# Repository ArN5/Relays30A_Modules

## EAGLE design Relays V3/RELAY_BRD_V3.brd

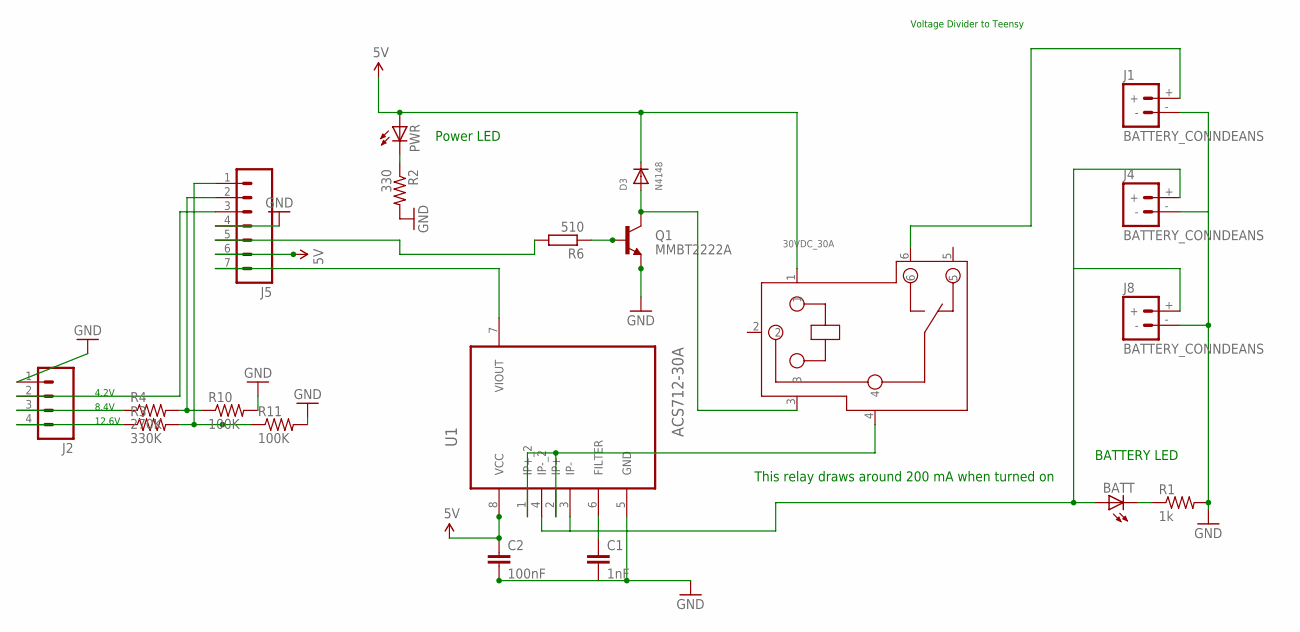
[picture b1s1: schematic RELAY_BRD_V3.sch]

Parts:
30VDC_30A: RELAY-SLA-05VDC-SL-C; 6P-19.8H
BATT: LED_E; LED_1206
C1: 1nF; 1206
C2: 100nF; 1206
D3: N4148; DO-1N4148
J1, J4, J8: BATTERY_CONNDEANS; DEANS
J2: M04POLAR; MOLEX-1X4
J5: M07LOCK_LONGPADS; 1X07_LOCK_LONGPADS
PWR: LED_E; LED_1206
Q1: MMBT2222A; SOT23-3
R1: 1k; 1206
R2: 330; 1206
R3: 330K; 1206
R4: 270K; 1206
R6: 510; R1206
R10, R11: 100K; 1206
U1: ACS712-30A; SOIC127P600X175-8N

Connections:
5V: 30VDC_30A.1, C2.1, D3.C, J5.6, PWR.A, U1.8 (VCC)
11.1V_BATTERY: 30VDC_30A.6, J1.+
CURRENT_SENSE: J5.7, U1.7 (VIOUT)
GND: C1.2, C2.2, J1.-, J2.1, J4.-, J5.4, J8.-, Q1.2 (E), R1.2, R2.2, R10.2, R11.2, U1.5 (GND)
unnamed: BATT.C, R1.1
unnamed: J5.5, R6.2
unnamed: PWR.C, R2.1
unnamed: Q1.1 (B), R6.1
unnamed: 30VDC_30A.3, D3.A, Q1.3 (C)
unnamed: J2.4, R3.1
unnamed: BATT.A, J4.+, J8.+, U1.3 (IP-), U1.4 (IP-_2)
unnamed: J2.3, R4.1
unnamed: C1.1, U1.6 (FILTER)
unnamed: J2.2, J5.3
unnamed: 30VDC_30A.4, U1.1 (IP+_2), U1.2 (IP+)
unnamed: J5.2, R4.2, R10.1
unnamed: J5.1, R3.2, R11.1

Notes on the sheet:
Voltage Divider to Teensy
This relay draws around 200 mA when turned on
Power LED
BATTERY LED
4.2V
8.4V
12.6V

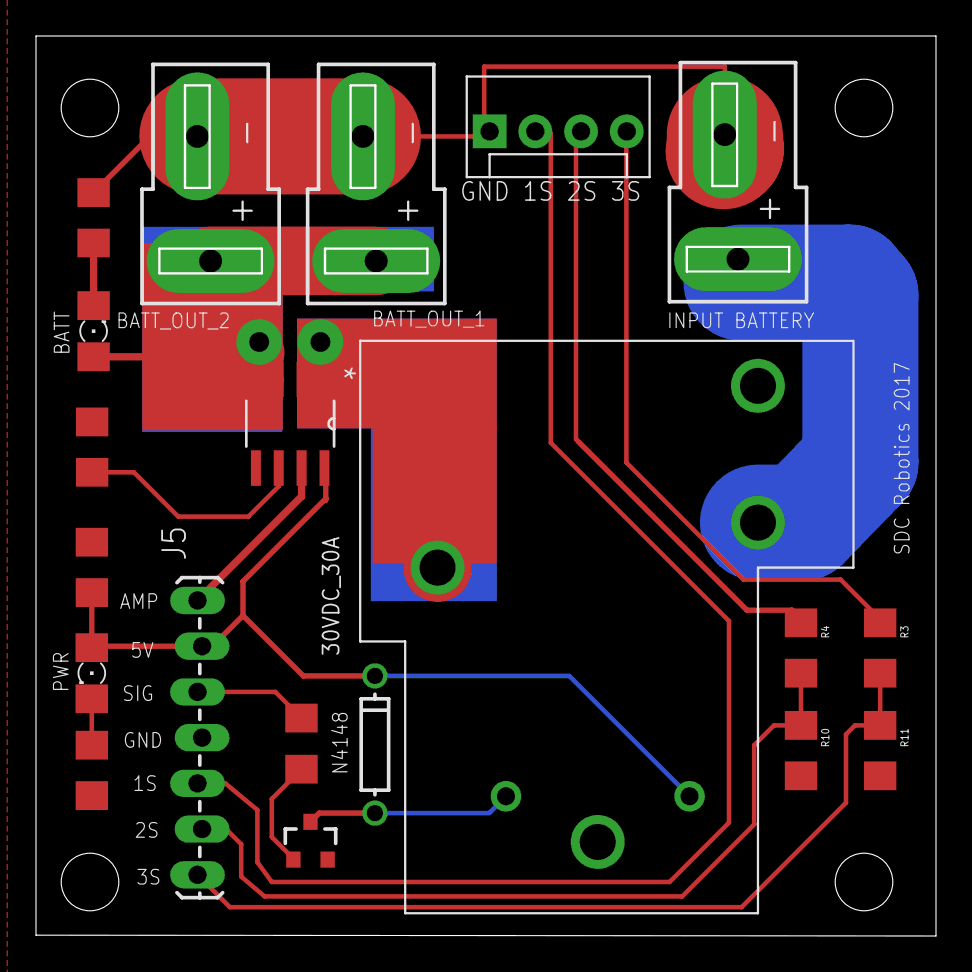
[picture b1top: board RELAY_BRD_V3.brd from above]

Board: 2 copper layers, 49.9 x 49.9 mm, 20 parts (0 on the bottom side), 17 nets.

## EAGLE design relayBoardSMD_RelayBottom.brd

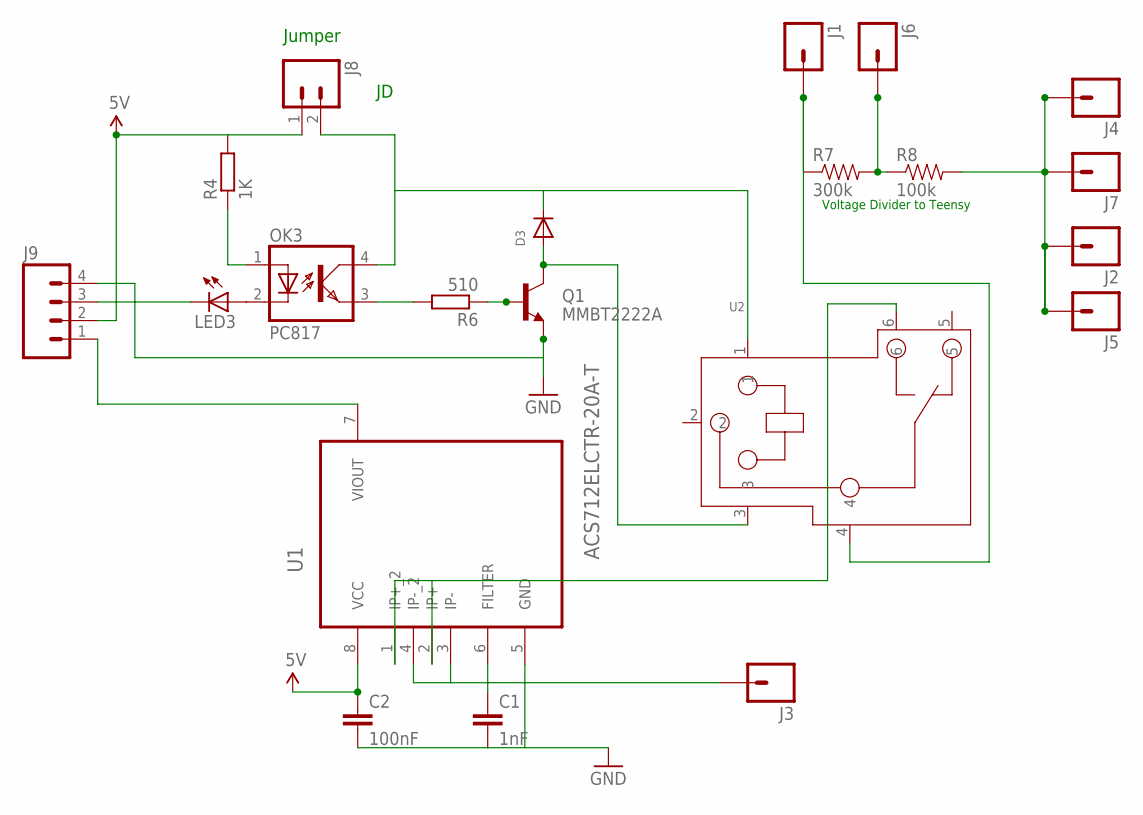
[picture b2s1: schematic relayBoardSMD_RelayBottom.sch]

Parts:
C1: 1nF; 1206
C2: 100nF; 1206
D3: DIODEDO-1N4148; DO-1N4148
J1, J2, J3, J4, J5, J6, J7: M01NOSILK-KIT; 1X01NS-KIT
J8: M02LOCK_LONGPADS; 1X02_LOCK_LONGPADS
J9: M04LOCK_LONGPADS; 1X04_LOCK_LONGPADS
LED3: LED_E; LED_1206
OK3: PC817; DIL04
Q1: MMBT2222A; SOT23-3
R4: 1K; R1206
R6: 510; R1206
R7: 300k; 1206
R8: 100k; 1206
U1: ACS712ELCTR-20A-T; SOIC127P600X175-8N
U2: RELAY-SLA-05VDC-SL-C; 6P-19.8H

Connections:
5V: C2.1, J8.1, J9.2, R4.2, U1.8 (VCC)
11.1V_BATTERY: J1.1, R7.1, U2.4
GND: C1.2, C2.2, J9.4, Q1.2 (E), U1.5 (GND)
GND_BATTERY: J2.1, J4.1, J5.1, J7.1, R8.2
unnamed: LED3.A, OK3.2 (C)
unnamed: OK3.1 (A), R4.1
unnamed: OK3.3 (EMIT), R6.2
unnamed: Q1.1 (B), R6.1
unnamed: D3.A, Q1.3 (C), U2.3
unnamed: D3.C, J8.2, OK3.4 (COL), U2.1
unnamed: J3.1, U1.3 (IP-), U1.4 (IP-_2)
unnamed: J9.3, LED3.C
unnamed: C1.1, U1.6 (FILTER)
unnamed: J9.1, U1.7 (VIOUT)
unnamed: U1.1 (IP+_2), U1.2 (IP+), U2.6
VOLTAGE_DIVIDER_5V: J6.1, R7.2, R8.1

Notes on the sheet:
Jumper
Voltage Divider to Teensy

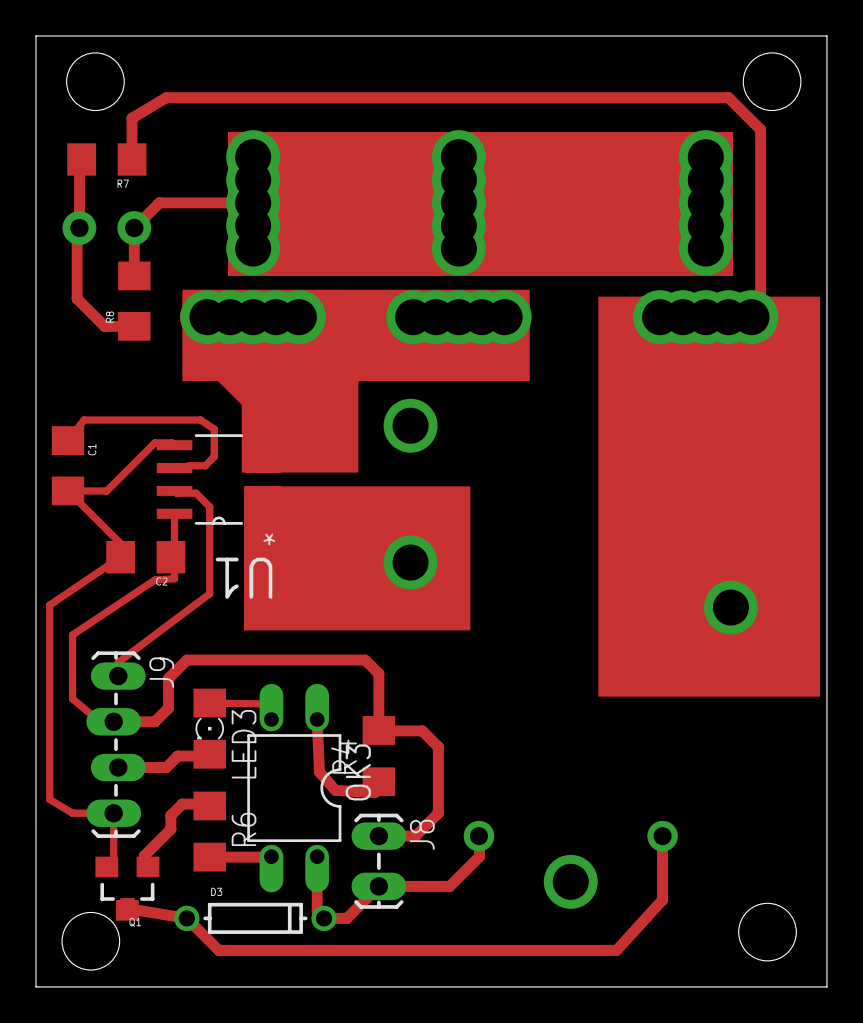
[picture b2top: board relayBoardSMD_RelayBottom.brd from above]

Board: 2 copper layers, 43.9 x 52.8 mm, 21 parts (1 on the bottom side), 16 nets.

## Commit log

2016-12-13 Relay 30 Amp Modules
    These Relays board have Dean connectors in order to avoid plugging
    incorrectly. They also need the ACS712 current sensor 30 amps. They may
    also measure the voltage across the battery connection. These board
    were designed as a Kill Switch for San Diego City Robotics for the
    Robosub competition.
2016-12-13 Led needed to be connected
2018-01-20 added relays v2
    added the new relays we will be using this year for robosub
2020-03-03 added the v3 version I made in 2017

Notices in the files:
parts and their libraries:
SparkFun-Connectors: Licensing: Creative Commons ShareAlike 4.0 International - https://creativecommons.org/licenses/by-sa/4.0
